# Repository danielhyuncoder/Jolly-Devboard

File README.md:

# Jolly-Devboard
A rp2040 devboard (followed from the guide) that is Christmas themed with red and green LEDs.
# Images:

# Bill of Materials (BOM)

| Item              | Description             | Qty | Product Link | Price w/ Tax ($) | Running Total ($) |
|-------------------|--------------------------|-----|--------------|------------------|--------------------|
| Capacitor         | 1uF                      | 2   | https://jlcpcb.com/partdetail/53938-CL05A105KA5NQNC/C52923 | $0.03 | $0.03 |
| Capacitor         | 0.1uF                    | 11  | https://jlcpcb.com/partdetail/1877-CL05B104KO5NNNC/C1525 | $0.21 | $0.24 |
| Capacitor         | 10uF                     | 2   | https://jlcpcb.com/partdetail/2043-CL10A106MQ8NNNC/C1691 | $0.18 | $0.42 |
| Capacitor         | 15pF                     | 2   | https://jlcpcb.com/partdetail/1914-0402CG150J500NT/C1547 | $0.01 | $0.43 |
| LED               | Indicator LED 0402       | 3   | https://jlcpcb.com/partdetail/Honglitronic-HL-LED0402R/C2290 | $0.06 | $0.49 |
| USB Receptacle    | USB-C 14P                | 1   | https://jlcpcb.com/partdetail/Korean_HropartsElec-TYPE_C_31_M12/C165948 | $0.85 | $1.34 |
| Conn_01x20        | Pin Header 1x20          | 2   | https://jlcpcb.com/partdetail/BOOMELE-BM20B-SRSS-TB/C358684 | $0.17 | $1.51 |
| Conn_01x03        | Pin Header 1x3           | 1   | https://jlcpcb.com/partdetail/BOOMELE-BM03B-SRSS-TB/C49257 | $0.05 | $1.56 |
| Resistor          | 5.1k                     | 1   | https://jlcpcb.com/partdetail/UNIROYAL-0402WGF5101TCE/C25905 | $0.01 | $1.57 |
| Resistor          | 5.2k                     | 1   | https://jlcpcb.com/partdetail/UNIROYAL-0402WGF5201TCE/C29120 | $0.01 | $1.58 |
| Resistor          | 27                       | 2   | https://jlcpcb.com/partdetail/UNIROYAL-0402WGF270JTCE/C25100 | $0.02 | $1.60 |
| Resistor          | 1k                       | 2   | https://jlcpcb.com/partdetail/UNIROYAL-0402WGF1001TCE/C11702 | $0.02 | $1.62 |
| Resistor          | 10k                      | 1   | https://jlcpcb.com/partdetail/UNIROYAL-0402WGF1002TCE/C25804 | $0.01 | $1.63 |
| SW_Push           | Tactile Button           | 1   | https://jlcpcb.com/partdetail/XKBConnectivity-TS1187ABAB/C318884 | $0.42 | $2.05 |
| RP2040            | Microcontroller          | 1   | https://jlcpcb.com/partdetail/RaspberryPi-RP2040/C2040 | $4.58 | $6.63 |
| Voltage Regulator | MCP1700-330 SOT-23       | 1   | https://jlcpcb.com/partdetail/MicrochipTech-MCP1700T_3302ETT/C39051 | $1.97 | $8.60 |
| Flash             | W25Q128JVS               | 1   | https://jlcpcb.com/partdetail/WinbondElec-W25Q128JVSIQ/C97521 | $2.67 | $11.27 |
| Crystal           | 12MHz 3225               | 1   | https://jlcpcb.com/partdetail/YXC_CrystalOscillators-X322512MSB4SI/C9002 | $0.32 | $11.59 |
| PCB Assembly      | Jolly Devboard PCB Assembly | 1 | N/A (https://cart.jlcpcb.com/) | $43.94 | $55.53 |

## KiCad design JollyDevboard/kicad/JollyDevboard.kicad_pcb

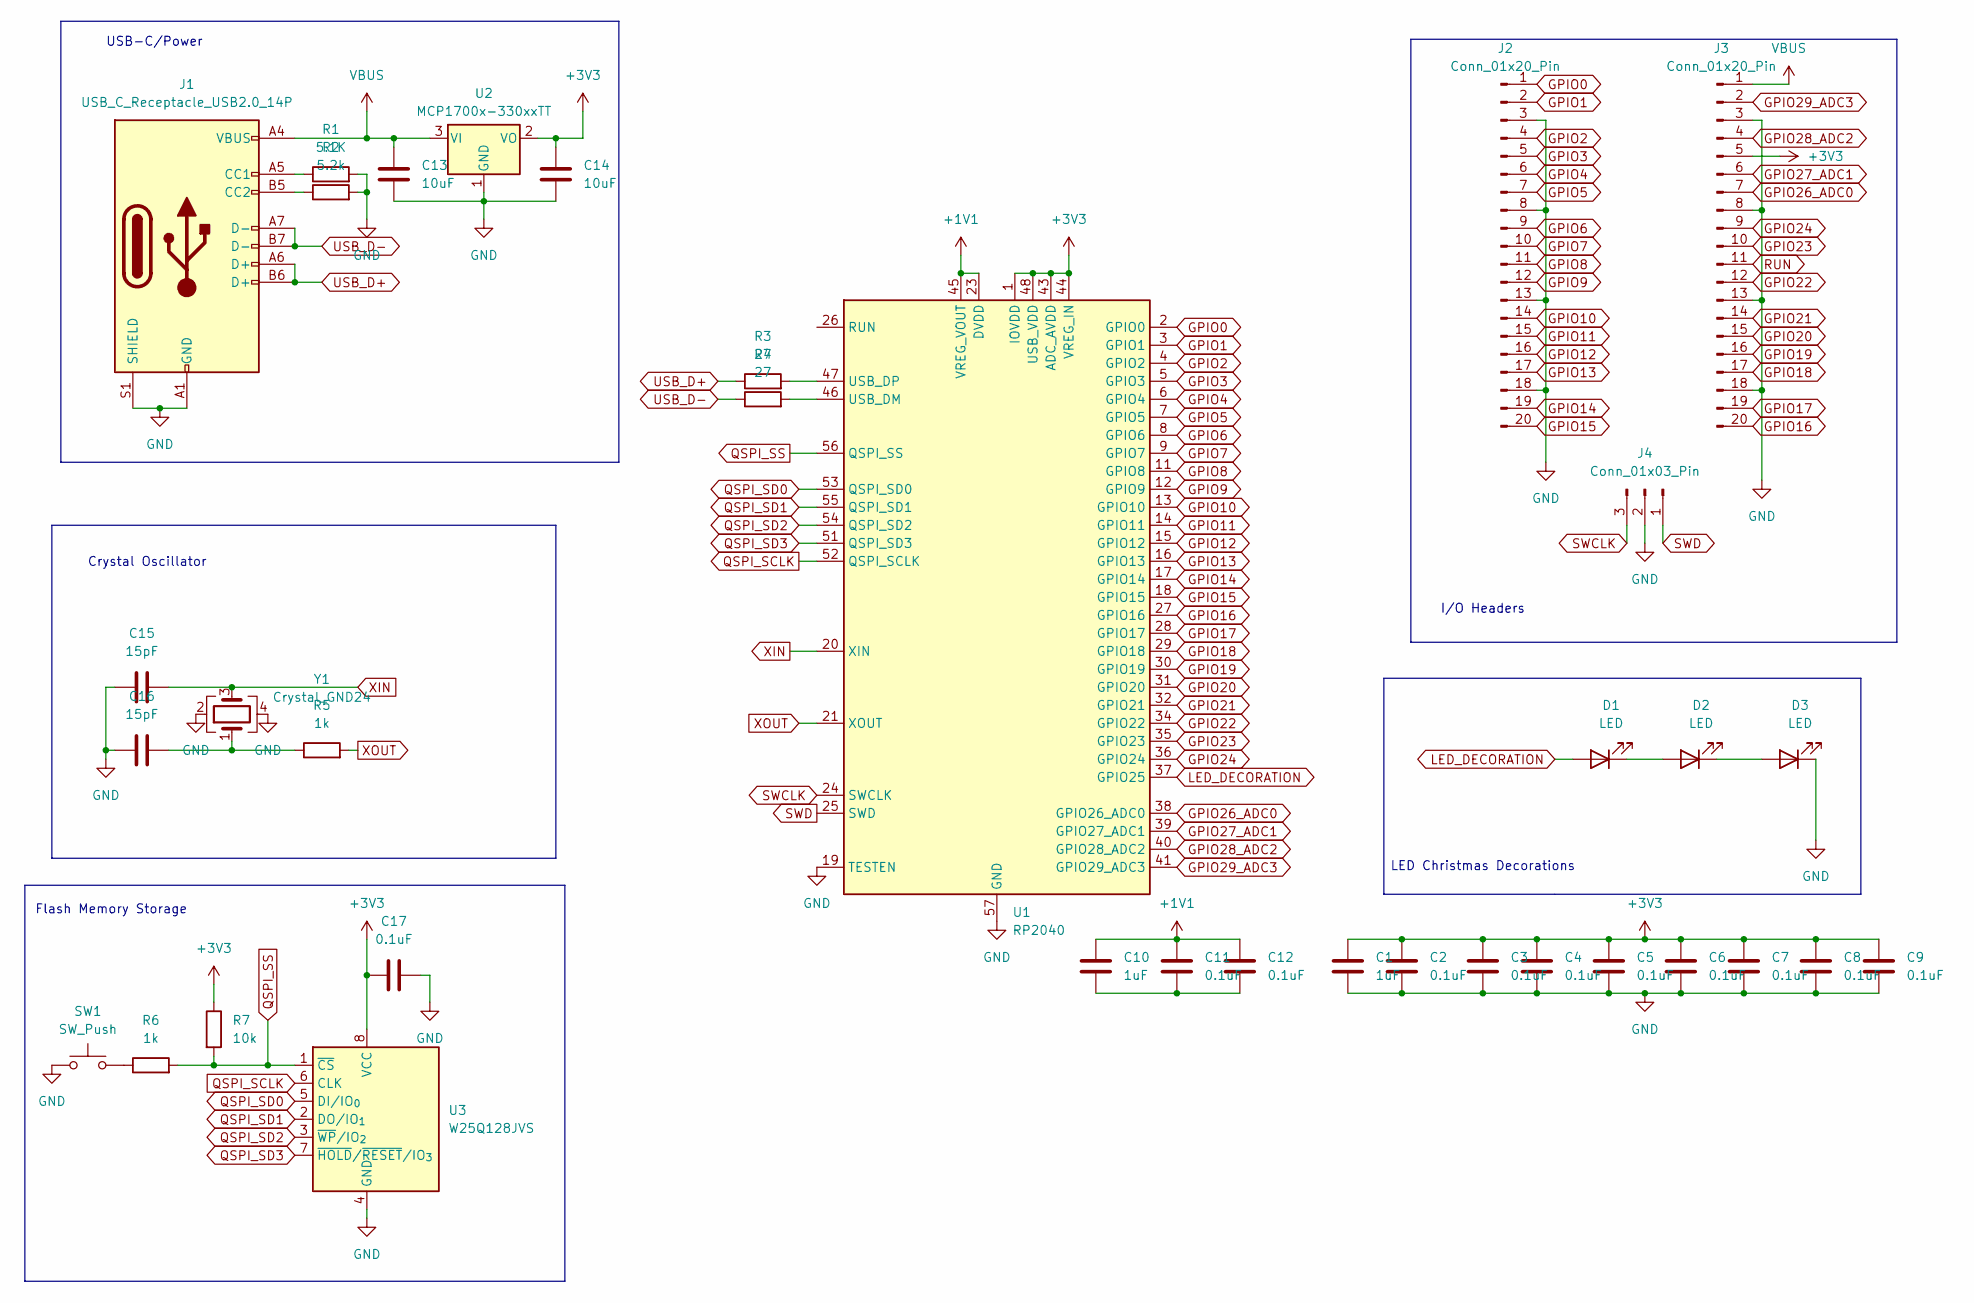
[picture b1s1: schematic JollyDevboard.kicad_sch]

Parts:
C1, C10: 1uF; C_0402_1005Metric
C2, C3, C4, C5, C6, C7, C8, C9, C11, C12, C17: 0.1uF; C_0402_1005Metric
C13, C14: 10uF; C_0402_1005Metric
C15, C16: 15pF; C_0402_1005Metric
D1, D2, D3: LED; LED_0402_1005Metric
J1: USB_C_Receptacle_USB2.0_14P; USB_C_Receptacle_HRO_TYPE-C-31-M-12
J2, J3: Conn_01x20_Pin; PinHeader_1x20_P2.54mm_Vertical
J4: Conn_01x03_Pin; PinHeader_1x03_P2.54mm_Vertical
R1: 5.1K; R_0402_1005Metric
R2: 5.2k; R_0402_1005Metric
R3, R4: 27; R_0402_1005Metric
R5, R6: 1k; R_0402_1005Metric
R7: 10k; R_0402_1005Metric
SW1: SW_Push; SW_Push_SPST_NO_Alps_SKRK
U1: RP2040; QFN-56-1EP_7x7mm_P0.4mm_EP3.2x3.2mm
U2: MCP1700x-330xxTT; SOT-23
U3: W25Q128JVS; SOIC-8_5.3x5.3mm_P1.27mm
Y1: Crystal_GND24; Crystal_SMD_3225-4Pin_3.2x2.5mm

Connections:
+1V1: C10.1, C11.1, C12.1, U1.23 (DVDD), U1.45 (VREG_VOUT), U1.50 (DVDD)
+3V3: C1.1, C2.1, C3.1, C4.1, C5.1, C6.1, C7.1, C8.1, C9.1, C14.1, C17.1, J3.5, R7.1, U1.1 (IOVDD), U1.10 (IOVDD), U1.22 (IOVDD), U1.33 (IOVDD), U1.42 (IOVDD), U1.43 (ADC_AVDD), U1.44 (VREG_IN), U1.48 (USB_VDD), U1.49 (IOVDD), U2.2 (VO), U3.8 (VCC)
GND: C1.2, C2.2, C3.2, C4.2, C5.2, C6.2, C7.2, C8.2, C9.2, C13.2, C14.2, C15.1, C16.1, C17.2, D3.1 (K), J1.A1 (GND), J1.A12 (GND), J1.B1 (GND), J1.B12 (GND), J1.S1 (SHIELD), J2.3, J2.8, J2.13, J2.18, J3.3, J3.8, J3.13, J3.18, J4.2, R1.2, R2.2, SW1.1, U1.19 (TESTEN), U1.57 (GND), U2.1 (GND), U3.4 (GND), Y1.2, Y1.4
GPIO0: J2.1, U1.2 (GPIO0)
GPIO1: J2.2, U1.3 (GPIO1)
GPIO2: J2.4, U1.4 (GPIO2)
GPIO3: J2.5, U1.5 (GPIO3)
GPIO4: J2.6, U1.6 (GPIO4)
GPIO5: J2.7, U1.7 (GPIO5)
GPIO6: J2.9, U1.8 (GPIO6)
GPIO7: J2.10, U1.9 (GPIO7)
GPIO8: J2.11, U1.11 (GPIO8)
GPIO9: J2.12, U1.12 (GPIO9)
GPIO10: J2.14, U1.13 (GPIO10)
GPIO11: J2.15, U1.14 (GPIO11)
GPIO12: J2.16, U1.15 (GPIO12)
GPIO13: J2.17, U1.16 (GPIO13)
GPIO14: J2.19, U1.17 (GPIO14)
GPIO15: J2.20, U1.18 (GPIO15)
GPIO16: J3.20, U1.27 (GPIO16)
GPIO17: J3.19, U1.28 (GPIO17)
GPIO18: J3.17, U1.29 (GPIO18)
GPIO19: J3.16, U1.30 (GPIO19)
GPIO20: J3.15, U1.31 (GPIO20)
GPIO21: J3.14, U1.32 (GPIO21)
GPIO22: J3.12, U1.34 (GPIO22)
GPIO23: J3.10, U1.35 (GPIO23)
GPIO24: J3.9, U1.36 (GPIO24)
GPIO26_ADC0: J3.7, U1.38 (GPIO26_ADC0)
GPIO27_ADC1: J3.6, U1.39 (GPIO27_ADC1)
GPIO28_ADC2: J3.4, U1.40 (GPIO28_ADC2)
GPIO29_ADC3: J3.2, U1.41 (GPIO29_ADC3)
LED_DECORATION: D1.2 (A), U1.37 (GPIO25)
unnamed: C10.2, C11.2, C12.2
unnamed: C16.2, R5.1, Y1.1
unnamed: D1.1 (K), D2.2 (A)
unnamed: D2.1 (K), D3.2 (A)
unnamed: J1.A5 (CC1), R1.1
unnamed: J1.B5 (CC2), R2.1
unnamed: R6.1, SW1.2
unnamed: R4.2, U1.46 (USB_DM)
unnamed: R3.2, U1.47 (USB_DP)
QSPI_SCLK: U1.52 (QSPI_SCLK), U3.6 (CLK)
QSPI_SD0: U1.53 (QSPI_SD0), U3.5 (DI/IO_{0})
QSPI_SD1: U1.55 (QSPI_SD1), U3.2 (DO/IO_{1})
QSPI_SD2: U1.54 (QSPI_SD2), U3.3 (~WP/IO_{2})
QSPI_SD3: U1.51 (QSPI_SD3), U3.7 (~HOLD/~RESET/IO_{3})
QSPI_SS: R6.2, R7.2, U1.56 (QSPI_SS), U3.1 (~CS)
RUN: J3.11
SWCLK: J4.3, U1.24 (SWCLK)
SWD: J4.1, U1.25 (SWD)
USB_D+: J1.A6 (D+), J1.B6 (D+), R3.1
USB_D-: J1.A7 (D-), J1.B7 (D-), R4.1
VBUS: C13.1, J1.A4 (VBUS), J1.A9 (VBUS), J1.B4 (VBUS), J1.B9 (VBUS), J3.1, U2.3 (VI)
XIN: C15.2, U1.20 (XIN), Y1.3
XOUT: R5.2, U1.21 (XOUT)

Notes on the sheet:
I/O Headers
LED Christmas Decorations
Flash Memory Storage
USB-C/Power
Crystal Oscillator

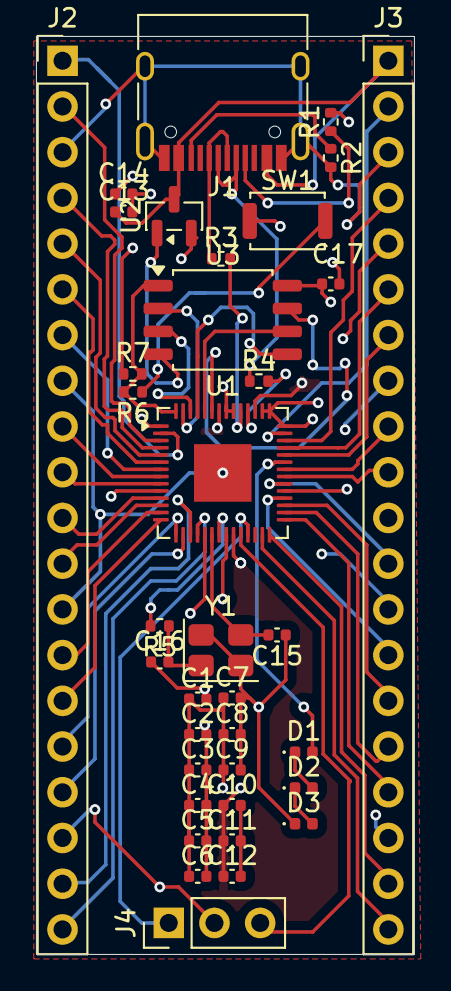
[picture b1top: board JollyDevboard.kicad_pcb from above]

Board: 4 copper layers, 21.0 x 51.0 mm, 36 parts (0 on the bottom side), 55 nets.

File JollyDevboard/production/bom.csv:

Designator,Footprint,Quantity,Value,LCSC Part #
"C1, C10",0402,2,1uF,C52923
"C11, C12, C17, C2, C3, C4, C5, C6, C7, C8, C9",0402,11,0.1uF,C1525
"C13, C14",0402,2,10uF,C15525
"C15, C16",0402,2,15pF,C1547
"D1, D2, D3",0402,3,LED,C2290
J1,USB_C_Receptacle_HRO_TYPE-C-31-M-12,1,USB_C_Receptacle_USB2.0_14P,C165948
"J2, J3",PinHeader_1x20_P2.54mm_Vertical,2,Conn_01x20_Pin,C358684
J4,PinHeader_1x03_P2.54mm_Vertical,1,Conn_01x03_Pin,C49257
R1,0402,1,5.1K,C25905
R2,0402,1,5.2k,C29120
"R3, R4",0402,2,27,C25100
"R5, R6",0402,2,1k,C11702
R7,0402,1,10k,C25804
SW1,SW_Push_SPST_NO_Alps_SKRK,1,SW_Push,C318884
U1,QFN-56-1EP_7x7mm_P0.4mm_EP3.2x3.2mm,1,RP2040,C2040
U2,SOT-23,1,MCP1700x-330xxTT,C39051
U3,SOIC-8_5.3x5.3mm_P1.27mm,1,W25Q128JVS,C97521
Y1,Crystal_SMD_3225-4Pin_3.2x2.5mm,1,Crystal_GND24,C9002

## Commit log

2025-12-06 project cm
2025-12-06 add readme details
    Expanded the README to include a detailed description, images, and a comprehensive Bill of Materials (BOM) for the Jolly-Devboard.
